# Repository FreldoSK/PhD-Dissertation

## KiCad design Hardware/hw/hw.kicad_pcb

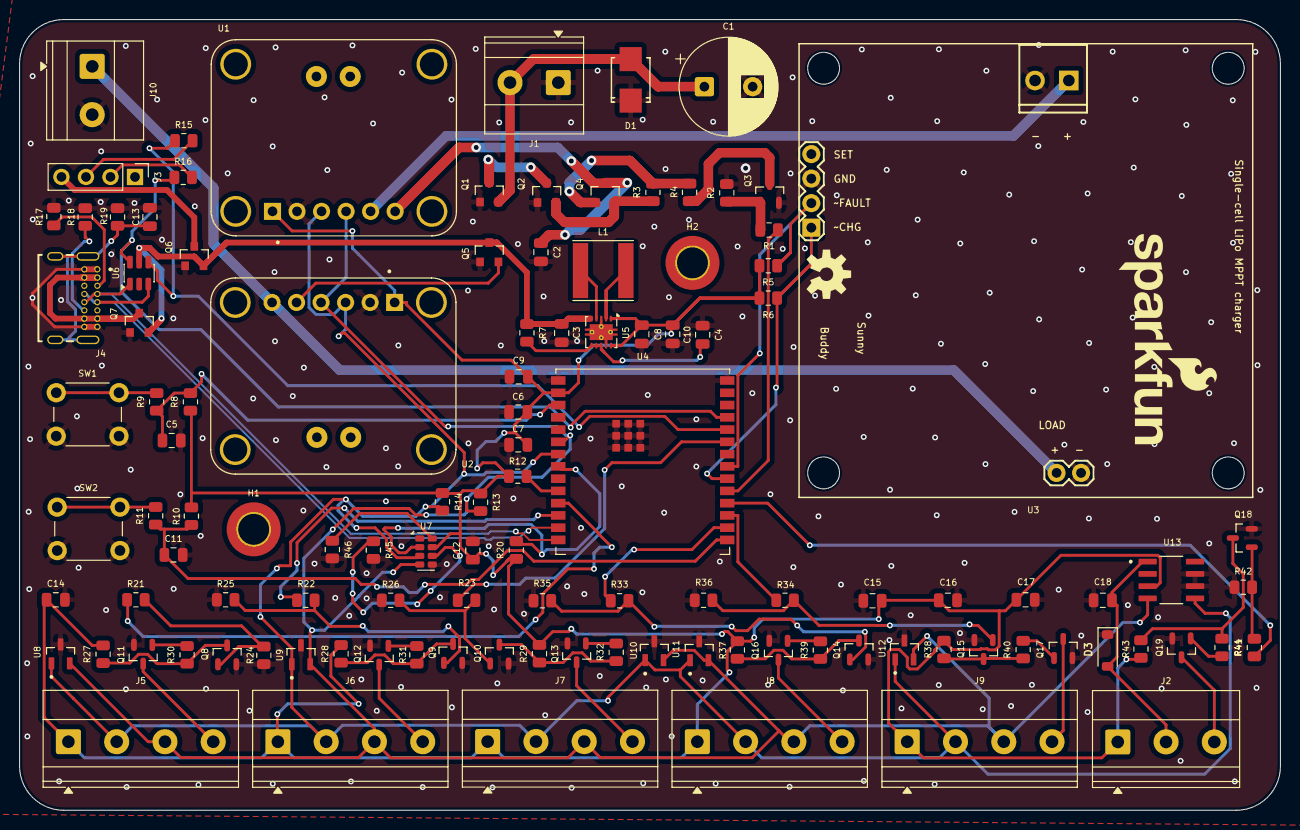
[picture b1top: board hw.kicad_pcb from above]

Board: 2 copper layers, 130.6 x 81.9 mm, 113 parts (0 on the bottom side), 71 nets.

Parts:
C1: 470u; CP_Radial_D10.0mm_P5.00mm
C2: 100n; C_0805_2012Metric
C3, C6, C8, C10, C15: 10uF; C_0805_2012Metric
C4, C5, C9, C11, C12, C14, C17, C18: 100nF; C_0805_2012Metric
C7, C16: 1uF; C_0805_2012Metric
C13: 1nF; C_0805_2012Metric
D1: SMBJ24CA:DO214AA; DO214AA
D3: 1N4448W; D_SOD-123
H1, H2: MountingHole; MountingHole_3.2mm_M3_DIN965_Pad_TopBottom
J1, J10: Screw_Terminal_01x02; TerminalBlock_Phoenix_MKDS-1,5-2_1x02_P5.00mm_Horizontal
J2: Screw_Terminal_01x03; TerminalBlock_Phoenix_MKDS-1,5-3_1x03_P5.00mm_Horizontal
J3: Conn_01x04_Pin; PinHeader_1x04_P2.54mm_Vertical
J4: USB4085-GF-A_REVA4; GCT_USB4085-GF-A_REVA4
J5, J6, J7, J8, J9: Screw_Terminal_01x04; TerminalBlock_Phoenix_MKDS-1,5-4_1x04_P5.00mm_Horizontal
L1: 2.2uH; L_Taiyo-Yuden_NR-60xx
Q1, Q2, Q4, Q5, Q6, Q7: PMOS; PMOS-SOT23
Q3, Q8, Q9, Q10, Q11, Q12, Q13, Q14, Q15, Q16, Q17, Q18, Q19: NMOS; AO3400A
R1, R4, R9, R11, R21, R22, R23, R30, R31, R32, R33, R34, R39, R40, R41, R44: 220; R_0805_2012Metric
R2, R5, R6, R8, R10, R20, R45, R46: 10k; R_0805_2012Metric
R3, R12, R24, R25, R26, R27, R28, R29, R35, R36, R37, R38, R42, R43: 100k; R_0805_2012Metric
R7: 100R; R_0805_2012Metric
R13, R14: 4k7; R_0805_2012Metric
R15, R16: 100; R_0805_2012Metric
R17, R18: 5k1; R_0805_2012Metric
R19: 1M; R_0805_2012Metric
SW1, SW2: SW_Push; SW_PUSH_6mm
U1, U2: INA219; MODULE_INA219
U3: SunnyBuddy:PRT-12885; PRT-12885
U4: ESP32-C6-WROOM-1; ESP32-C6-WROOM-1U
U5: TPS63001; Texas_DRC0010J_ThermalVias
U6: USBLC6-4SC6; SOT-23-6
U7: RV-3028-C7; MicroCrystal_C7_SON-8_1.5x3.2mm_P0.9mm
U8, U9, U10, U11, U12: PESD5V0L2BT,215; SOT95P230X110-3N
U13: MCP3422A0-E/SN; SOIC127P600X175-8N

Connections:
+3V3: C6.1, C7.1, C8.1, C9.1, C10.1, C12.1, C14.1, C15.1, C16.1, C17.1, J2.1, J5.1, J6.1, J7.1, J8.1, J9.1, R5.1, R6.1, R8.1, R10.1, R12.1, R13.1, R14.1, R20.1, R27.2, R28.2, R29.2, R37.2, R38.2, R43.2, U1.1 (VCC), U2.1 (VCC), U4.2 (3V3), U5.1 (VOUT), U5.10 (FB), U7.7 (VDD), U13.3 (Vdd)
ADC: C18.1, D3.2 (A), J2.2, U13.1 (CH1+)
BOOT: C11.1, R10.2, R11.1, U4.15 (GPIO9)
CHG: R6.2, U3.6 (CHG), U4.20 (GPIO22)
Data+: J4.A6 (DP1), J4.B6 (DP2), U4.14 (GPIO13/USB_D+), U6.1 (I/O1)
Data-: J4.A7 (DN1), J4.B7 (DN2), U4.13 (GPIO12/USB_D-), U6.3 (I/O2)
FAULT: R5.2, U3.5 (FAULT), U4.21 (GPIO23)
GND: C1.2, C2.2, C3.2, C4.2, C5.2, C6.2, C7.2, C8.2, C9.2, C10.2, C11.2, C12.2, C13.2, C14.2, C15.2, C16.2, C17.2, C18.2, D1.1, D3.1 (K), J1.1, J3.1, J4.A1 (GND), J4.A12 (GND), J4.B1 (GND), J4.B12 (GND), J10.2, Q1.2 (G), Q2.2 (G), Q3.3 (S), Q5.2 (G), Q6.2 (G), Q7.2 (G), Q8.3 (S), Q9.3 (S), Q10.3 (S), Q11.3 (S), Q12.3 (S), Q13.3 (S), Q14.3 (S), Q15.3 (S), Q16.3 (S), Q17.3 (S), Q18.3 (S), Q19.3 (S), R2.2, R17.2, R18.2, R19.1, R24.1, R25.1, R26.1, R35.1, R36.1, R42.1, R45.2, R46.2, SW1.2, SW2.2, U1.2 (GND), U2.2 (GND), U3.2 (Sol-), U3.4 (GND), U3.8 (LOAD-), U4.1 (GND), U4.28 (GND), U4.29 (GND), U5.3 (PGND), U5.9 (GND), U5.11 (PGND), U6.2 (GND), U7.5 (VSS), U8.3 (GND), U9.3 (GND), U10.3 (GND), U11.3 (GND), U12.3 (GND), U13.6 (Vss), U13.8 (CH2+)
GPIO0: R20.2, U4.8 (GPIO0/ADC1_CH0/XTAL_32K_P), U7.2 (~INT)
GPIO8: R12.2, U4.10 (GPIO8)
GPIO10: R21.1, U4.11 (GPIO10)
GPIO11: R22.1, U4.12 (GPIO11)
GPIO15: R23.1, U4.23 (GPIO15)
GPIO18: R33.1, U4.16 (GPIO18)
GPIO19: R34.1, U4.17 (GPIO19)
GPIO20: R41.1, U4.18 (GPIO20)
GPIO21: R1.1, U4.19 (GPIO21)
I2C_SCL: J5.2, J6.2, J7.2, J8.2, J9.2, R14.2, U1.3 (SCL), U2.3 (SCL), U4.7 (MTDO/GPIO7), U7.3 (SCL), U8.1 (IO1), U9.1 (IO1), U10.1 (IO1), U11.1 (IO1), U12.1 (IO1), U13.5 (SCL)
I2C_SDA: J5.3, J6.3, J7.3, J8.3, J9.3, R13.2, U1.4 (SDA), U2.4 (SDA), U4.6 (MTCK/GPIO6/ADC1_CH6), U7.4 (SDA), U8.2 (IO2), U9.2 (IO2), U10.2 (IO2), U11.2 (IO2), U12.2 (IO2), U13.4 (SDA)
Load: J10.1, U2.6 (VIN+), U3.7 (LOAD+)
unnamed: C13.1, J4.S1 (SHELL), J4.S2 (SHELL), J4.S3 (SHELL), J4.S4 (SHELL), R19.2
unnamed: C1.1, D1.2, J1.2, Q1.3 (S)
unnamed: J2.3, Q19.1 (D)
unnamed: J3.2, R16.2
unnamed: J3.3, R15.2
unnamed: J3.4, Q6.1 (D)
unnamed: J4.A5 (CC1), R17.1
unnamed: J4.B5 (CC2), R18.1
unnamed: J5.4, Q11.1 (D)
unnamed: J6.4, Q12.1 (D)
unnamed: J7.4, Q13.1 (D)
unnamed: J8.4, Q16.1 (D)
unnamed: J9.4, Q17.1 (D)
unnamed: Q1.1 (D), Q2.1 (D)
unnamed: Q2.3 (S), Q4.3 (S), R3.1
unnamed: Q3.1 (D), R4.2
unnamed: Q3.2 (G), R1.2, R2.1
unnamed: Q4.2 (G), R3.2, R4.1
unnamed: Q5.3 (S), U2.5 (VIN-)
unnamed: Q8.1 (D), R27.1, R30.1
unnamed: Q8.2 (G), R21.2, R24.2
unnamed: Q9.1 (D), R28.1, R31.1
unnamed: Q9.2 (G), R22.2, R25.2
unnamed: Q10.1 (D), R29.1, R32.1
unnamed: Q10.2 (G), R23.2, R26.2
unnamed: Q11.2 (G), R30.2
unnamed: Q12.2 (G), R31.2
unnamed: Q13.2 (G), R32.2
unnamed: Q14.1 (D), R37.1, R39.1
unnamed: Q14.2 (G), R33.2, R35.2
unnamed: Q15.1 (D), R38.1, R40.1
unnamed: Q15.2 (G), R34.2, R36.2
unnamed: Q16.2 (G), R39.2
unnamed: Q17.2 (G), R40.2
unnamed: Q18.1 (D), R43.1, R44.1
unnamed: Q18.2 (G), R41.2, R42.2
unnamed: Q19.2 (G), R44.2
unnamed: R9.2, SW1.1
unnamed: R11.2, SW2.1
unnamed: C4.1, R7.2, U5.6 (EN), U5.7 (PS/SYNC), U5.8 (VINA)
unnamed: L1.1, U5.4 (L1)
unnamed: L1.2, U5.2 (L2)
unnamed: R46.1, U7.8 (EVI)
unnamed: R45.1, U7.6 (VBACKUP)
RST: C5.1, R8.2, R9.1, U4.3 (EN/CHIP_PU)
ToDCDC: C3.1, Q5.1 (D), Q6.3 (S), Q7.3 (S), R7.1, U5.5 (VIN), U6.5 (VBUS)
UART_RX: R15.1, U4.24 (U0RXD/GPIO17), U6.4 (I/O3)
UART_TX: R16.1, U4.25 (U0TXD/GPIO16), U6.6 (I/O4)
VBUS: J4.A4 (VBUS), J4.A9 (VBUS), J4.B4 (VBUS), J4.B9 (VBUS), Q7.1 (D)
Vin+: C2.1, Q4.1 (D), U1.6 (VIN+)
Vin-: U1.5 (VIN-), U3.1 (Sol+)

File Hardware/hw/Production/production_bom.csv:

Designator,Footprint,Quantity,Value,LCSC Part #
C1,CP_Radial_D10.0mm_P5.00mm,1,470u,
"C10, C15, C3, C6, C8",0805,5,10uF,
"C11, C12, C14, C17, C18, C4, C5, C9",0805,8,100nF,
C13,0805,1,1nF,
"C16, C7",0805,2,1uF,
C2,0805,1,100n,
D1,DO214AA,1,SMBJ24CA:DO214AA,
D2,D_SOD-323,1,STS321050B100-EA,
"J1, J2","TerminalBlock_Phoenix_MKDS-1,5-2-5.08_1x02_P5.08mm_Horizontal",2,Screw_Terminal_01x02,
J10,"TerminalBlock_Phoenix_MKDS-1,5-3-5.08_1x03_P5.08mm_Horizontal",1,Screw_Terminal_01x03,
J3,PinHeader_1x04_P2.54mm_Vertical,1,Conn_01x04_Pin,
J4,GCT_USB4085-GF-A_REVA4,1,USB4085-GF-A_REVA4,
"J5, J6, J7, J8, J9","TerminalBlock_Phoenix_MKDS-1,5-4-5.08_1x04_P5.08mm_Horizontal",5,Screw_Terminal_01x04,
L1,L_Taiyo-Yuden_NR-60xx,1,2.2uH,
"Q1, Q2, Q4, Q5, Q6, Q7",PMOS-SOT23,6,PMOS,
"Q10, Q11, Q12, Q13, Q14, Q15, Q16, Q17, Q18, Q19, Q3, Q8",SOT95P230X110-3N,12,NMOS,
Q9,AO3400A,1,NMOS,
"R1, R11, R21, R22, R23, R30, R31, R32, R33, R34, R39, R4, R40, R41, R44, R9",0805,16,220,
"R10, R2, R20, R5, R6, R8",0805,6,10k,
"R12, R24, R25, R26, R27, R28, R29, R3, R35, R36, R37, R38, R42, R43",0805,14,100k,
"R13, R14",0805,2,4k7,
"R15, R16",0805,2,100,
"R17, R18",0805,2,5k1,
R19,0805,1,1M,
R7,0805,1,100R,
"SW1, SW2",SW_PUSH_6mm,2,SW_Push,
"U1, U2",MODULE_INA219,2,INA219,
"U10, U11, U12, U8, U9",SOT95P230X110-3N,5,"PESD5V0L2BT,215",
U13,SOIC127P600X175-8N,1,MCP3422A0-E/SN,
U3,PRT-12885,1,SunnyBuddy:PRT-12885,
U4,ESP32-C6-WROOM-1U,1,ESP32-C6-WROOM-1,
U5,Texas_DRC0010J_ThermalVias,1,TPS63001,
U6,SOT-23-6,1,USBLC6-4SC6,
U7,MicroCrystal_C7_SON-8_1.5x3.2mm_P0.9mm,1,RV-3028-C7,

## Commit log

2025-12-08 init commit
2026-02-09 Research update
2026-02-10 Nové články
2026-02-23 Scheme update
2026-02-25 lib update
2026-02-26 Charging update
2026-02-27 HW update
2026-03-03 lil update
2026-03-03 SMS3.3.TCT update
2026-04-14 IoT board update
2026-04-15 IoT update
2026-04-20 USB and UART update
2026-04-21 Big update
2026-04-21 little update
2026-04-22 Sensors update
2026-04-23 Anemometer update
2026-04-24 Hardware v1.0
2026-04-27 External ADC update
2026-04-28 Tomáš update
2026-05-14 Mega update
2026-05-15 new PCB
2026-05-26 Addaptive Control
2026-05-28 Stupid-Stupid update
2026-05-29 RTC update
2026-06-01 home work
2026-06-02 Screw matrix update
2026-06-03 PCB update
